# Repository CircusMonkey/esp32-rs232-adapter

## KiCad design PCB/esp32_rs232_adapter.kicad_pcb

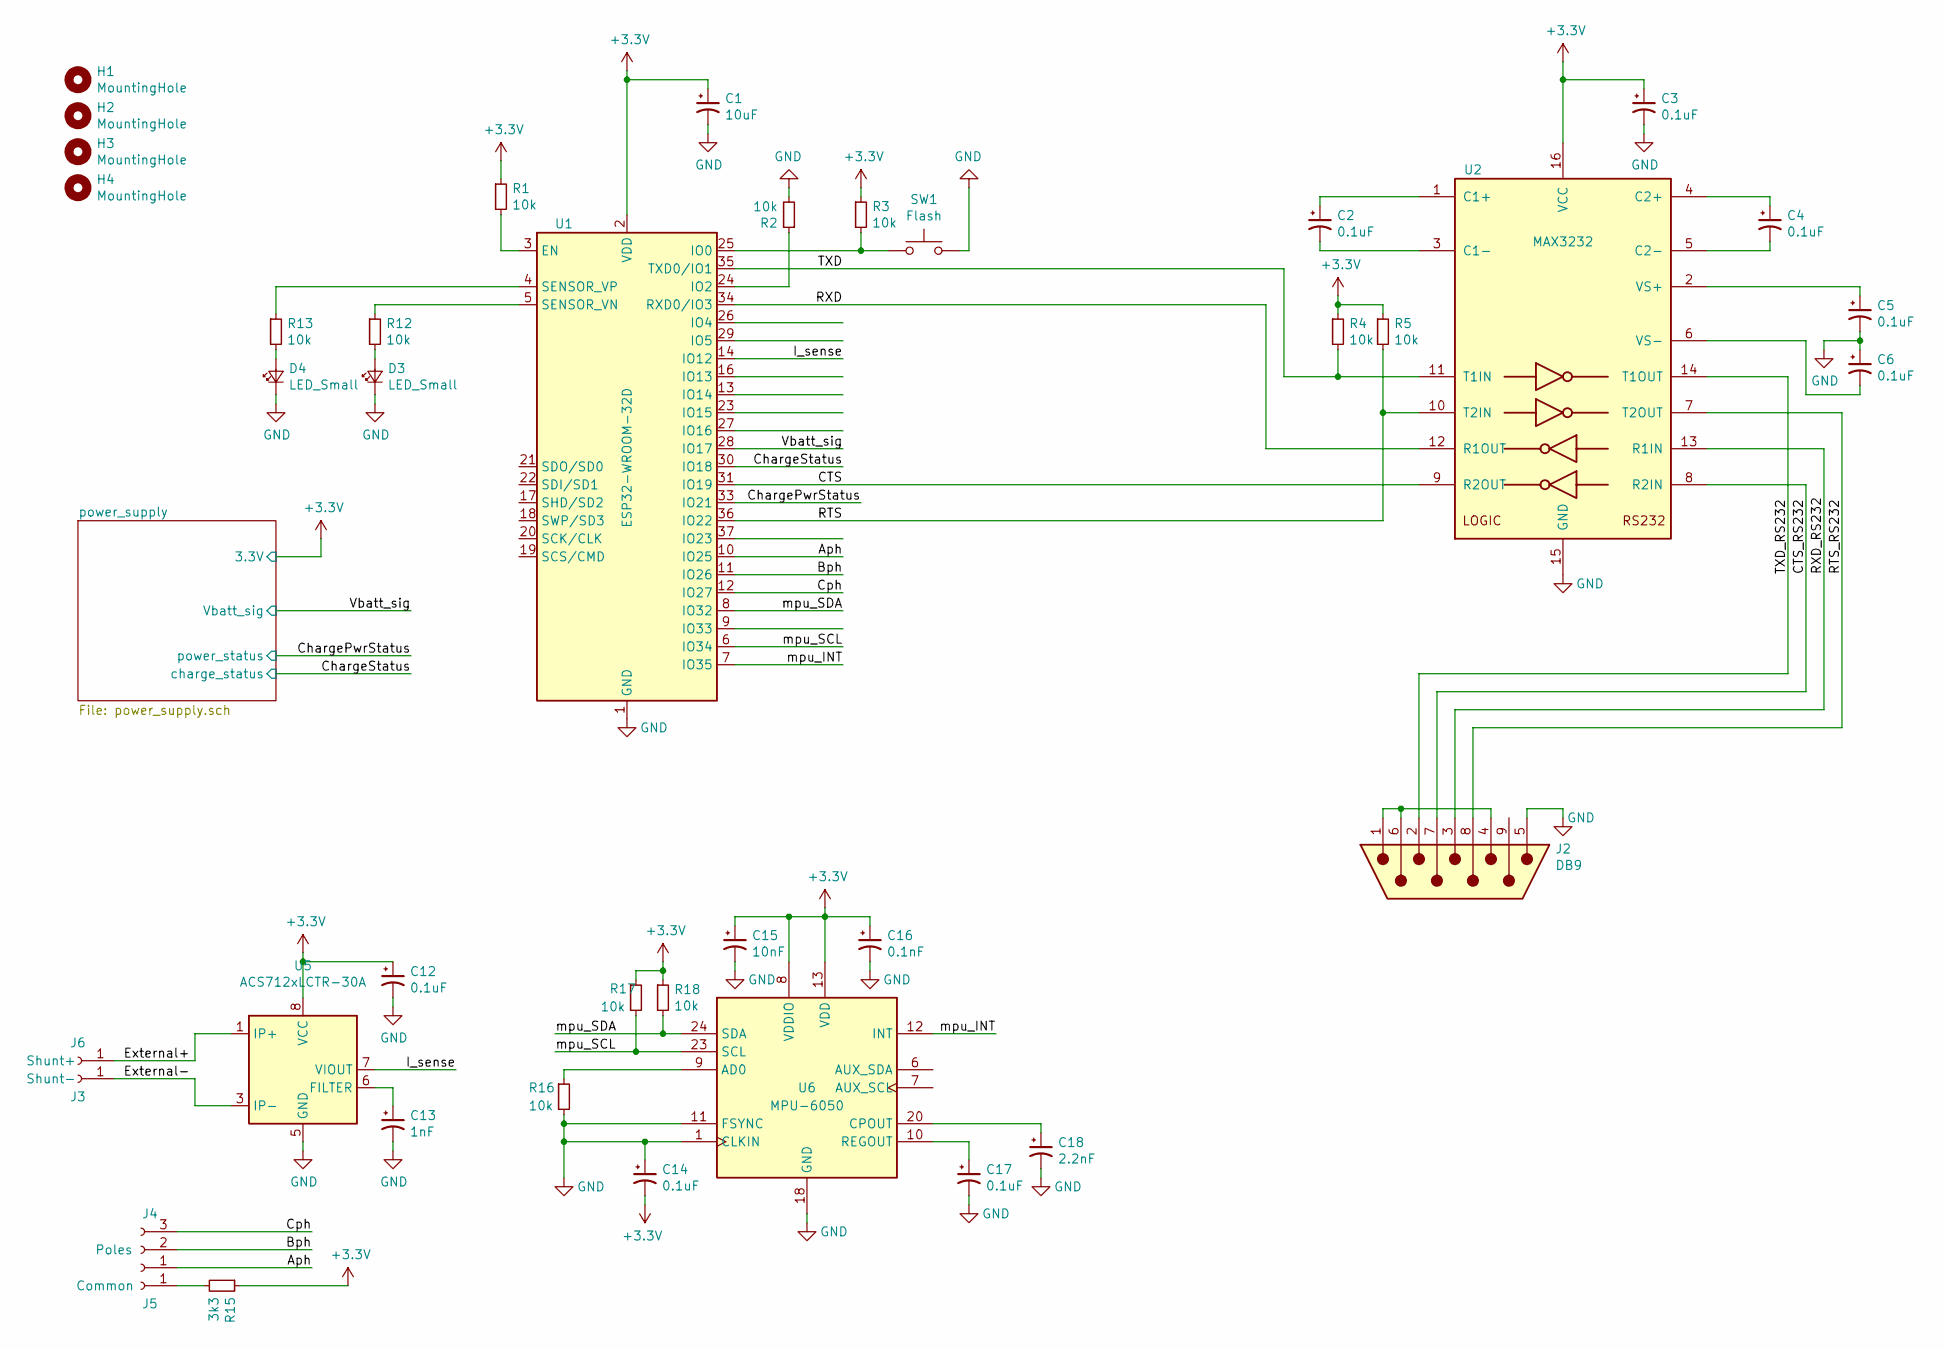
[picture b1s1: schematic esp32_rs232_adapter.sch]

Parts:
C1: 10uF; C_0805_2012Metric
C2, C3, C4, C5, C6, C12, C14, C17: 0.1uF; C_0805_2012Metric
C13: 1nF; C_0805_2012Metric
C15: 10nF; C_0805_2012Metric
C16: 0.1nF; C_0805_2012Metric
C18: 2.2nF; C_0805_2012Metric
D3, D4: LED_Small; LED_0805_2012Metric
H1, H2, H3, H4: MountingHole; MountingHole_3.2mm_M3_ISO7380
J2: DB9; DSUB-9_Male_Horizontal_P2.77x2.84mm_EdgePinOffset4.94mm_Hou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
J3: Shunt-; Banana_Jack_1Pin
J4: Poles; Banana_Jack_3Pin
J5: Common; Banana_Jack_1Pin
J6: Shunt+; Banana_Jack_1Pin
R1, R2, R3, R4, R5, R12, R13, R16, R17, R18: 10k; R_0805_2012Metric
R15: 3k3; R_0805_2012Metric
SW1: Flash; SW_SPST_B3S-1000
U1: ESP32-WROOM-32D; ESP32-WROOM-32-Heat
U2: MAX3232; SOP-16_4.55x10.3mm_P1.27mm
U5: ACS712xLCTR-30A; SOIC-8_3.9x4.9mm_P1.27mm
U6: MPU-6050; InvenSense_QFN-24_4x4mm_P0.5mm

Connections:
+3V3: C1.1, C3.1, C12.1, C14.2, C15.1, C16.1, R1.1, R3.1, R4.1, R5.1, R15.1, R17.1, R18.1, U1.2 (VDD), U2.16 (VCC), U5.8 (VCC), U6.8 (VDDIO), U6.13 (VDD); also elsewhere on the board
/Aph: J4.1, U1.10 (IO25)
/Bph: J4.2, U1.11 (IO26)
/CTS: U1.31 (IO19), U2.9 (R2OUT)
/CTS_RS232: J2.7, U2.8 (R2IN)
/ChargePwrStatus: U1.33 (IO21); also elsewhere on the board
/ChargeStatus: U1.30 (IO18); also elsewhere on the board
/Cph: J4.3, U1.12 (IO27)
/External+: J6.1, U5.1 (IP+), U5.2 (IP+)
/External-: J3.1, U5.3 (IP-), U5.4 (IP-)
/I_sense: U1.14 (IO12), U5.7 (VIOUT)
/RTS: R5.2, U1.36 (IO22), U2.10 (T2IN)
/RTS_RS232: J2.8, U2.7 (T2OUT)
/RXD: U1.34 (RXD0/IO3), U2.12 (R1OUT)
/RXD_RS232: J2.3, U2.13 (R1IN)
/TXD: R4.2, U1.35 (TXD0/IO1), U2.11 (T1IN)
/TXD_RS232: J2.2, U2.14 (T1OUT)
/Vbatt_sig: U1.28 (IO17); also elsewhere on the board
/mpu_INT: U1.7 (IO35), U6.12 (INT)
/mpu_SCL: R17.2, U1.6 (IO34), U6.23 (SCL)
/mpu_SDA: R18.2, U1.8 (IO32), U6.24 (SDA)
GND: C1.2, C3.2, C5.2, C6.1, C12.2, C13.2, C14.1, C15.2, C16.2, C17.2, C18.2, D3.1 (K), D4.1 (K), J2.5, R2.2, R16.2, SW1.2, U1.1 (GND), U1.15 (GND), U1.38 (GND), U2.15 (GND), U5.5 (GND), U6.1 (CLKIN), U6.11 (FSYNC), U6.18 (GND); also elsewhere on the board
unnamed: C2.1, U2.1 (C1+)
unnamed: C2.2, U2.3 (C1-)
unnamed: C4.1, U2.4 (C2+)
unnamed: C4.2, U2.5 (C2-)
unnamed: C5.1, U2.2 (VS+)
unnamed: C6.2, U2.6 (VS-)
unnamed: C13.1, U5.6 (FILTER)
unnamed: C17.1, U6.10 (REGOUT)
unnamed: C18.1, U6.20 (CPOUT)
unnamed: D3.2 (A), R12.2
unnamed: D4.2 (A), R13.2
unnamed: J2.1, J2.4, J2.6
unnamed: J5.1, R15.2
unnamed: R1.2, U1.3 (EN)
unnamed: R2.1, U1.24 (IO2)
unnamed: R3.2, SW1.1, U1.25 (IO0)
unnamed: R12.1, U1.5 (SENSOR_VN)
unnamed: R13.1, U1.4 (SENSOR_VP)
unnamed: R16.1, U6.9 (AD0)

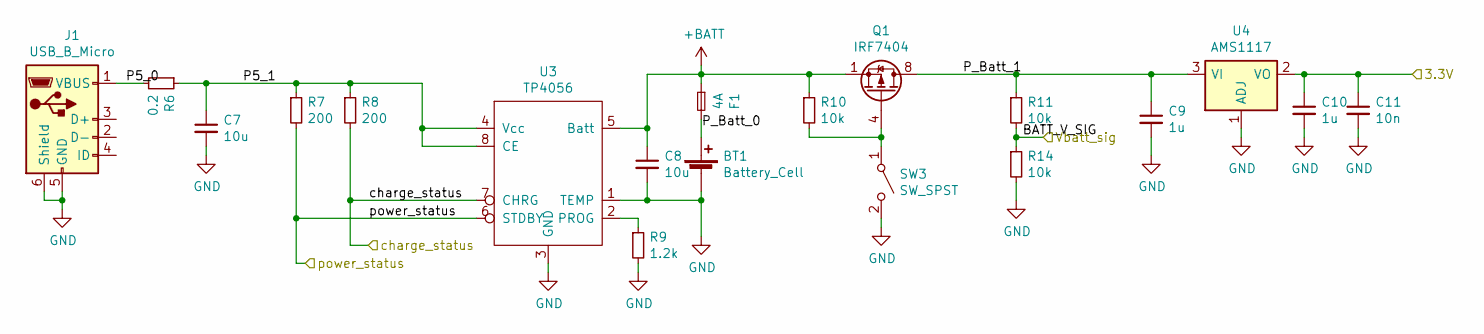
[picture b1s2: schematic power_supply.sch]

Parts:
BT1: Battery_Cell; JST_PH_B2B-PH-K_1x02_P2.00mm_Vertical
C7, C8: 10u; C_0805_2012Metric
C9, C10: 1u; C_0805_2012Metric
C11: 10n; C_0805_2012Metric
F1: 4A; Fuse_1206_3216Metric
J1: USB_B_Micro; USB_Micro-B_Molex-105017-0001
Q1: IRF7404; SOIC-8_3.9x4.9mm_P1.27mm
R6: 0.2; R_0805_2012Metric
R7, R8: 200; R_0805_2012Metric
R9: 1.2k; R_0805_2012Metric
R10, R11, R14: 10k; R_0805_2012Metric
SW3: SW_SPST; SW_CuK_JS202011CQN_DPDT_Straight
U3: TP4056; SSOP-8_3.9x5.05mm_P1.27mm
U4: AMS1117; SOT-223-3_TabPin2

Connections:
+3V3: C10.1, C11.1, U4.2 (VO); also elsewhere on the board
+BATT: C8.1, F1.1, Q1.1 (S), Q1.2 (S), Q1.3 (S), R10.1, U3.5 (Batt)
/ChargePwrStatus: R7.2, U3.6 (STDBY); also elsewhere on the board
/ChargeStatus: R8.2, U3.7 (CHRG); also elsewhere on the board
/Vbatt_sig: R11.2, R14.1; also elsewhere on the board
/power_supply/P5_0: J1.1 (VBUS), R6.2
/power_supply/P5_1: C7.1, R6.1, R7.1, R8.1, U3.4 (Vcc), U3.8 (CE)
/power_supply/P_Batt_0: BT1.1 (+), F1.2
/power_supply/P_Batt_1: C9.1, Q1.5 (D), Q1.6 (D), Q1.7 (D), Q1.8 (D), R11.1, U4.3 (VI)
GND: BT1.2 (-), C7.2, C8.2, C9.2, C10.2, C11.2, J1.5 (GND), J1.6 (Shield), R9.2, R14.2, SW3.2 (B), U3.1 (TEMP), U3.3 (GND), U4.1 (ADJ); also elsewhere on the board
unnamed: Q1.4 (G), R10.2, SW3.1 (A)
unnamed: R9.1, U3.2 (PROG)

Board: 2 copper layers, 59 parts (16 on the bottom side), 48 nets, no tracks yet.

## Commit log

2019-02-26 Starting PCB
2019-03-03 work on schematics
2019-03-04 Nearly finished schematic
2019-03-05 remove .lib files from gitignore
2019-03-13 change footprints. Add dip switch for null modem
2019-03-13 More footprint swaps
2019-03-24 PCB finished
2019-03-24 Forgot to save before committing last time :|
2019-03-24 remove via in through hole
2019-04-30 work in progress with stuff for cb testing
2019-05-11 Updated pin assignments
2019-11-04 remove null modem switch
